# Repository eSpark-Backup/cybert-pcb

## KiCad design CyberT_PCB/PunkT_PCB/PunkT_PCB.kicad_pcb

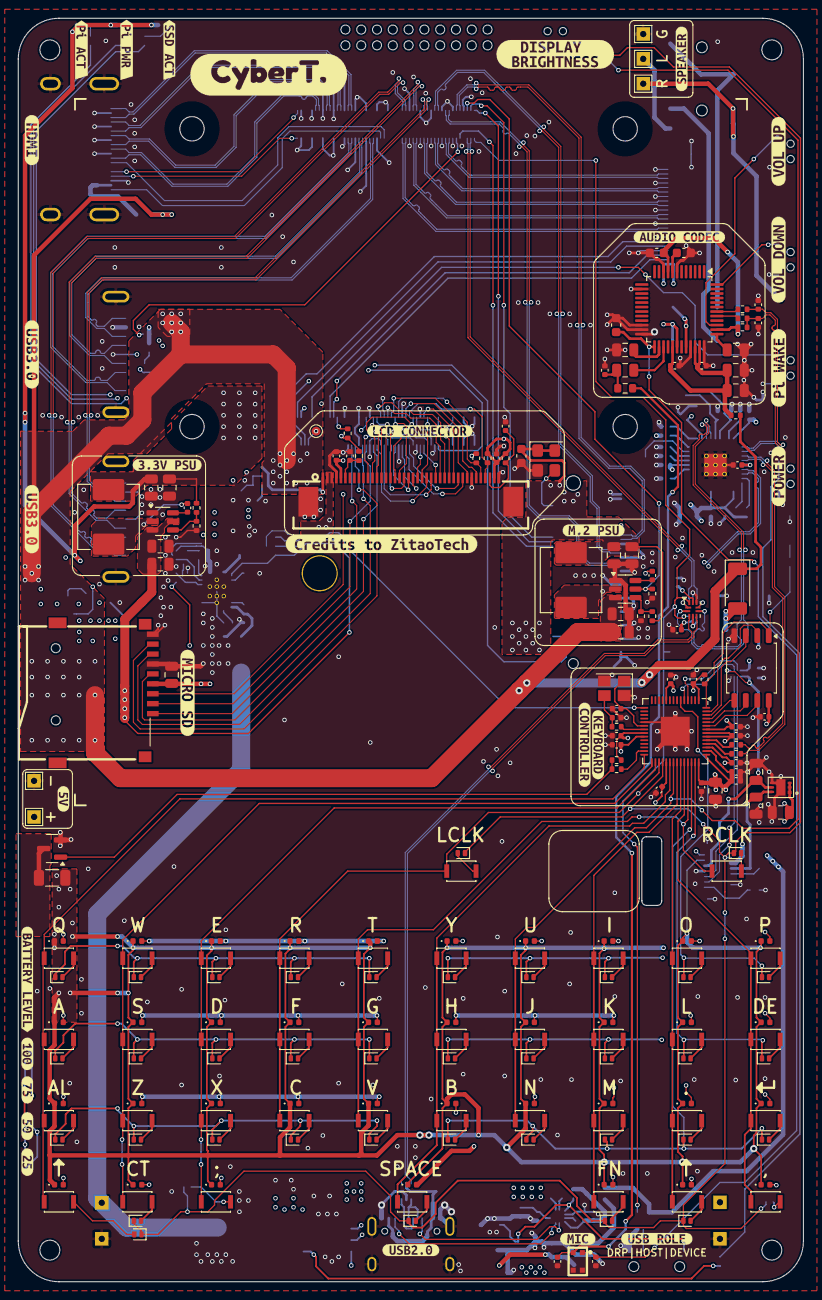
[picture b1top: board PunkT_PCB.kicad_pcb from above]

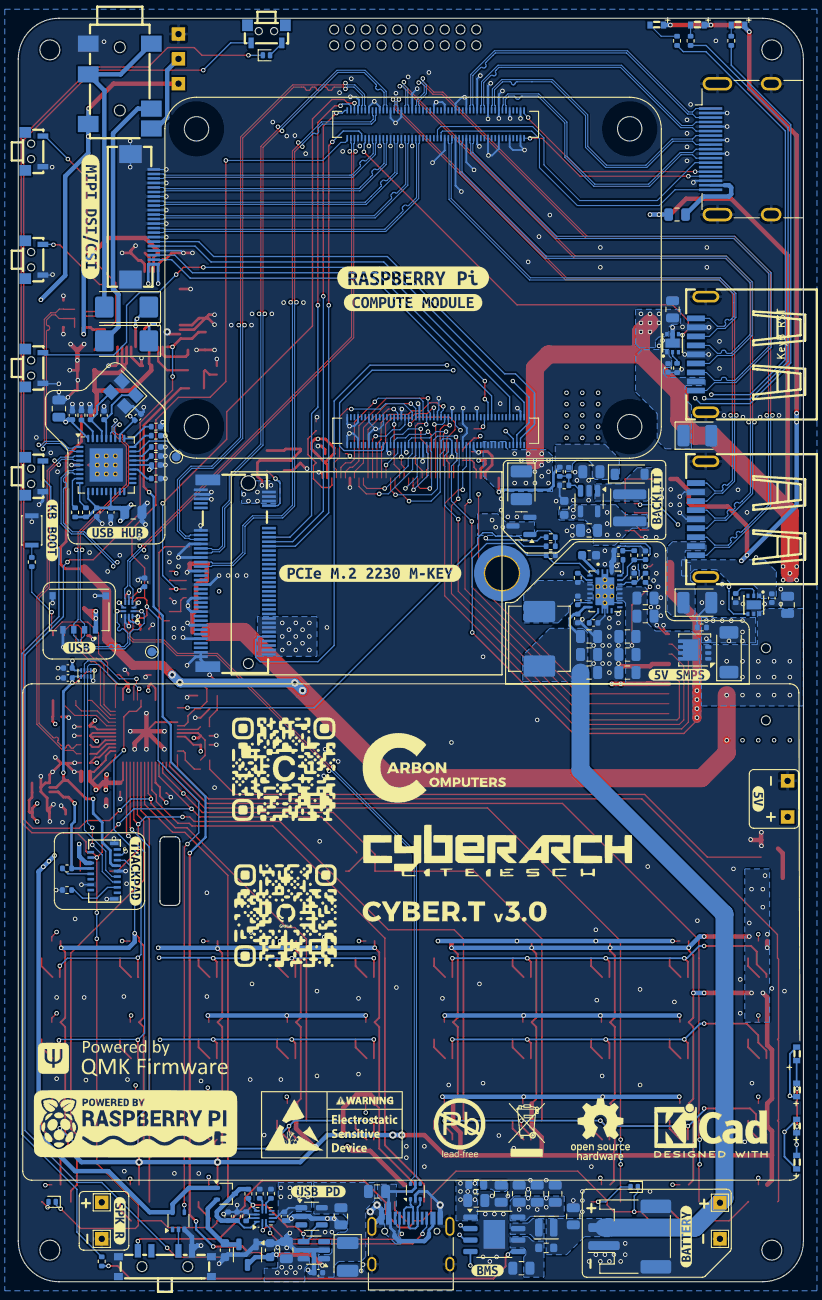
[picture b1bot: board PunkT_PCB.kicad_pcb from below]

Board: 4 copper layers, 87.0 x 140.0 mm, 405 parts (166 on the bottom side), 271 nets.

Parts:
C1, C4: 15pF; C_0402_1005Metric
C2, C10, C11, C13, C14, C15, C19, C21, C26, C30, C31, C36, C39, C43, C44, C49, C59, C60, C66, C79, C98, C101, C309, C312: 10uF; C_0805_2012Metric
C3, C5, C6, C7, C8, C9, C23, C25, C33, C40, C42, C47, C51, C56, C57, C61, C69, C70, C72, C73, C74, C75, C76, C77, C78, C81, C82, C86, C88, C96, C99, C100, C102: 0.1uF; C_0402_1005Metric
C12, C48, C58, C97: 100uF; CP_EIA-3528-21_Kemet-B
C16, C17: 470uF; CP_EIA-6032-28_Kemet-C
C18, C20: 100pF; C_0402_1005Metric
C22, C32: 22pF; C_0402_1005Metric
C24, C41, C71: 100nF; C_0402_1005Metric
C27, C28, C29, C80, C105: 4.7uF; C_0603_1608Metric
C34, C35: 33pF; C_0402_1005Metric
C37, C38, C45, C46, C50, C52, C53, C62, C63, C65, C83, C84, C85, C91, C93, C103, C104: 22uF; C_0805_2012Metric
C64: 0.1uF; C_0603_1608Metric
C67, C68, C95: 1uF; C_0402_1005Metric
C87, C310: 2.2uF; C_0603_1608Metric
C90: 8.2nF; C_0402_1005Metric
C92: 1nF; C_0402_1005Metric
C94: 47pF; C_0402_1005Metric
C311: 220pF; C_0402_1005Metric
D1, D6, D7, D8, D9, D11, D12, D13, D14, D15, D16, D17, D18, D20, D21, D22, D25, D26, D27, D30, D31, D32, D33, D35, D36, D37, D40, D41, D42, D43, D45, D46, D47, D48, D50, D51, D52, D53, D77, D81: D; D_SOD-882D
D2: PMEG2010ER,115; D_SOD-123
D3: Pi ACT; LED-SMD_XL-1606
D4: RPI PWR; LED-SMD_XL-1606
D10: PMEG4030EP,115; D_SOD-128
D19: LD1; LED-SMD_XL-1606
D23: LD2; LED-SMD_XL-1606
D24: LD3; LED-SMD_XL-1606
D28: LD4; LED-SMD_XL-1606
D29, D34, D38, D39, D44, D49, D54, D55, D56, D57, D58, D59, D60, D61, D62, D63, D64, D65, D66, D67, D68, D69, D70, D71, D72, D73, D74, D76, D78, D79, D80, D82, D83, D84, D85, D86, D87: LED; LED_0402_1005Metric
D75: BAT54CW; SOT-323_SC-70
D88: PCIe ACT; LED-SMD_XL-1606
D89: PMEG4050EP; D_SOD-128
F1: 200mA; Fuse_0805_2012Metric
H5: KEY; MountingHole_2.7mm_M2.5_DIN965_Pad_TopBottom
J1: SPK_L; TestPoint_THTPad_1.5x1.5mm_Drill0.7mm
J2: HDMI_A_1.4; HDMI_A_Molex_208658-1001_Horizontal
J3: CSI 1; FFC-SMD_22P-P0.50_X05A20L22T
J4, J21: SPK_R; TestPoint_THTPad_1.5x1.5mm_Drill0.7mm
J5: Micro_SD_Card; TF-SMD_TF-01A
J6, J22: SPK_GND; TestPoint_THTPad_1.5x1.5mm_Drill0.7mm
J7: USB; MOLEX_0781710004
J8: BATTERY; JST_PH_S2B-PH-SM4-TB_1x02-1MP_P2.00mm_Horizontal
J9: AFC07-S40ECA-00
J10: BAT+; TestPoint_THTPad_1.5x1.5mm_Drill0.7mm
J11: HEADPHONE; AUDIO-SMD_PJ-3420-A-SMT_C319102
J12: BAT-; TestPoint_THTPad_1.5x1.5mm_Drill0.7mm
J13: TYPE C; USB_C_Receptacle_HRO_TYPE-C-31-M-12
J14: FH35C-17S-0.3SHW(50); FPC-SMD_17P-P0.60_HRS_FH35C-17S-0.3SHW
J15, J16: CM5; REF
J17: Bus_M.2_Socket_M; PCI-APCI0079-P002A
J18, J19: U-A-39DS-Y-1
J20: display; REF
J23: +5V; TestPoint_THTPad_1.5x1.5mm_Drill0.7mm
J24: GND; TestPoint_THTPad_1.5x1.5mm_Drill0.7mm
L1: BLM18BD252SN1; R_0603_1608Metric
L2: 1uH; L_Sunlord_SWPA252012S
L3, L5: MWSA0618S-2R2MT; L_Sunlord_MWSA0618S
L4: MWSA0624S-1R0MT; L_Sunlord_MWSA0624S
L9: PSBHAA201210H-681T040; C_0805_2012Metric
L30: SWPA4012S100MT; L_Sunlord_SWPA4010S
Q1: DMP3013SFV; Diodes_PowerDI3333-8
Q2, Q3: AO3400A; SOT-23
R1: 2R; R_0603_1608Metric
R2, R8, R21, R24, R29, R33, R35, R44, R46, R50, R51: 10k; R_0402_1005Metric
R3, R4, R18, R19, R52: 1k; R_0402_1005Metric
R5: 120k; R_0402_1005Metric
R6, R41: 33.2k; R_0402_1005Metric
R7, R14, R42: 0R; R_0402_1005Metric
R9, R22, R26, R27, R53: 100k; R_0402_1005Metric
R10, R11, R13, R15: 36k; R_0402_1005Metric
R12: 12k; R_0402_1005Metric
R16, R17, R43, R45: 22R; R_0402_1005Metric
R20: 10.5k; R_0402_1005Metric
R23: 1.5k; R_0402_1005Metric
R25, R28, R30: 10K; R_0402_1005Metric
R31, R38: 15k; R_0402_1005Metric
R32, R49: 220R; R_0402_1005Metric
R34: 10R; R_1206_3216Metric
R36: 0.5R; R_0603_1608Metric
R39, R40: 5.1k; R_0402_1005Metric
R56: 267k; R_0402_1005Metric
R57: 113k; R_0402_1005Metric
R58: 23.7k; R_0402_1005Metric
R59: 220k; R_0402_1005Metric
R60: 69.8k; R_0402_1005Metric
SW1: PI WAKEUP; KEY-SMD_TX-1010-X-X
SW2: RESET; SW_SPST_CK_KXT3
SW3: VOL DWN; KEY-SMD_TX-1010-X-X
SW4, SW5, SW6, SW7, SW9, SW10, SW11, SW12, SW13, SW14, SW15, SW16, SW18, SW19, SW20, SW22, SW23, SW24, SW25, SW26, SW28, SW29, SW30, SW31, SW33, SW34, SW35, SW38, SW39, SW40, SW41, SW43, SW44, SW45, SW46, SW48, SW49, SW50, SW51: key; SW_SPST_CK_KXT3
SW8: VOL UP; KEY-SMD_TX-1010-X-X
SW17: POWER; KEY-SMD_TX-1010-X-X
SW21: DIPLAY BACKLIT; KEY-SMD_TX-1010-X-X
SW27: SSSS812201
TP5, TP11: nEXTRST; TestPoint_Pad_D1.0mm
TP12: nPiBOOT; TestPoint_Pad_D1.0mm
U1, U15: TPS565208DDCR; SOT-23-6
U2: TXS0102DQE; X2SON-8_1.4x1mm_P0.35mm
U3: USB2514B_Bi; QFN-36-1EP_6x6mm_P0.5mm_EP3.7x3.7mm_ThermalVias
U5, U16: TS3USB30ERSWR; UQFN-10_1.4x1.8mm_P0.4mm
U6: RPi-CM5; Raspberry-Pi-5-Compute-Module
U7: SN74LVC1G07DCKR; SOT-353_SC-70-5
U8: S15OT421-005; MIC-SMD_4P-L2.8-W1.9_S15OT421-005
U9: CM108; LQFP-48_7x7mm_P0.5mm
U10: USBLC6-2P6; SOT-666
U12, U13: AP2553FDC-7; WDFN-6_L2.0-W2.0-P0.65-BL-EP-1
U17: RP2040; QFN-56-1EP_7x7mm_P0.4mm_EP3.2x3.2mm
U18: IP5306; HTSOP-8-1EP_3.9x4.9mm_P1.27mm_EP2.4x3.2mm
U19: W25Q128JVS; SOIC-8_5.3x5.3mm_P1.27mm
U21: VRD1828MLX; LLP-6_L2.0-W1.8-P0.50-BL-EP
U22: TPS61088RHLR; IC_TPS61088RHLR
U23: XC6206PxxxMR; SOT-23-3
U25: FUSB303BTMX; Texas_X2QFN-12_1.6x1.6mm_P0.4mm
U26: AP22814AW5; SOT-23-5
U27: AP22814BW5; SOT-23-5
U57: LMR62014XMFX; SOT-23-5
Y1: 24MHz; Crystal_SMD_Abracon_ABM8G-4Pin_3.2x2.5mm
Y2: 12MHz; Crystal_SMD_SeikoEpson_FA238-4Pin_3.2x2.5mm
Y3: OK2JI-111-32.768K; Oscillator_SMD_SiT_PQFN-4Pin_3.2x2.5mm
kibuzzard-68A0B5B4: G***; kibuzzard-68A0B5B4
kibuzzard-68A0B5DF: G***; kibuzzard-68A0B5DF
kibuzzard-68A0B7F3: G***; kibuzzard-68A0B7F3
kibuzzard-68A0B20E: G***; kibuzzard-68A0B20E
kibuzzard-68A0B54C, kibuzzard-68A0B54C#2: G***; kibuzzard-68A0B54C
kibuzzard-68A0B61C: G***; kibuzzard-68A0B61C
kibuzzard-68A0B62B: G***; kibuzzard-68A0B62B
kibuzzard-68A0B64B: G***; kibuzzard-68A0B64B
kibuzzard-68A0B71E: G***; kibuzzard-68A0B71E
kibuzzard-68A0B217: G***; kibuzzard-68A0B217
kibuzzard-68A0B281: G***; kibuzzard-68A0B281
kibuzzard-68A0B510: G***; kibuzzard-68A0B510
kibuzzard-68A0B518: G***; kibuzzard-68A0B518
kibuzzard-68A0B535: G***; kibuzzard-68A0B535
kibuzzard-68A0B569: G***; kibuzzard-68A0B569
kibuzzard-68A0B633: G***; kibuzzard-68A0B633
kibuzzard-68A0B676: G***; kibuzzard-68A0B676
kibuzzard-68A0B778: G***; kibuzzard-68A0B778
kibuzzard-68A0B782: G***; kibuzzard-68A0B782
kibuzzard-68A77CD8: G***; kibuzzard-68A77CD8
kibuzzard-68A77CF1: G***; kibuzzard-68A77CF1
kibuzzard-68A77E8B: G***; kibuzzard-68A77E8B
kibuzzard-68A770D3, kibuzzard-68A770D3#2: G***; kibuzzard-68A770D3
kibuzzard-68A771D4: G***; kibuzzard-68A771D4
kibuzzard-68A772E8: G***; kibuzzard-68A772E8
kibuzzard-68A773B1: G***; kibuzzard-68A773B1
kibuzzard-68A777A6: G***; kibuzzard-68A777A6
kibuzzard-68A777CE: G***; kibuzzard-68A777CE
kibuzzard-68A777FF: G***; kibuzzard-68A777FF
kibuzzard-68A778E8: G***; kibuzzard-68A778E8
kibuzzard-68A778EF: G***; kibuzzard-68A778EF
kibuzzard-68A778FF: G***; kibuzzard-68A778FF
kibuzzard-68A788C5: G***; kibuzzard-68A788C5
kibuzzard-68A7778C: G***; kibuzzard-68A7778C
kibuzzard-68A7792B: G***; kibuzzard-68A7792B
kibuzzard-68A77223: G***; kibuzzard-68A77223
kibuzzard-68A77349: G***; kibuzzard-68A77349
kibuzzard-68A77437: G***; kibuzzard-68A77437
kibuzzard-68A77588: G***; kibuzzard-68A77588
kibuzzard-68A77715: G***; kibuzzard-68A77715
kibuzzard-68A77820: G***; kibuzzard-68A77820
kibuzzard-68A77953: G***; kibuzzard-68A77953
kibuzzard-68A79058: G***; kibuzzard-68A79058

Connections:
+1V1: C67.1, C69.1, C70.1, U17.23 (DVDD), U17.45 (VREG_VOUT), U17.50 (DVDD)
+1V8: C19.1, C24.1, J14.7, U2.1 (VCCA), U2.5 (OE), U21.5 (VOUT1)
+2V8: C15.1, J14.8, R35.1, U21.6 (VOUT2)
+3.3V: C2.1, C3.1, C5.1, C6.1, C7.1, C8.1, C9.1, C10.1, C11.1, C14.1, C40.1, C41.1, C42.1, C56.1, C57.1, C68.1, C71.1, C72.1, C73.1, C74.1, C75.1, C76.1, C77.1, C78.1, C79.1, C103.1, C104.1, D3.2 (A), D4.2 (A), D75.1, D88.2 (A), J3.22, J5.4 (VDD), J9.5, J9.39, J14.6, L5.2, R6.1, R14.1, R21.2, R22.1, R25.2, R28.2, R30.2, R39.1, R40.1, R42.1, R50.1, R51.1, U2.8 (VCCB), U3.5 (VDDA33), U3.10 (VDDA33), U3.15 (VDD33), U3.23 (VDD33), U3.29 (VDDA33), U3.36 (VDDA33), U5.9 (VCC), U7.5 (VCC), U16.9 (VCC), U17.1 (IOVDD), U17.10 (IOVDD), U17.22 (IOVDD), U17.33 (IOVDD), U17.42 (IOVDD), U17.43 (ADC_AVDD), U17.44 (VREG_IN), U17.48 (USB_VDD), U17.49 (IOVDD), U19.8 (VCC), U21.1 (EN2), U21.2 (VIN), U21.3 (EN1)
+3.3VP: C62.1, C63.1, C64.1, J17.2 (3.3V), J17.4 (3.3V), J17.12 (3.3V), J17.14 (3.3V), J17.16 (3.3V), J17.18 (3.3V), J17.70 (3.3V), J17.72 (3.3V), J17.74 (3.3V), L3.2, R41.1, Y3.1 (OE), Y3.4 (Vdd)
+5V: C12.1, C44.1, C49.1, C59.1, C60.1, C101.1, C309.1, C310.1, D10.1 (K), D29.2 (A), D34.2 (A), D38.2 (A), D39.2 (A), D44.2 (A), D49.2 (A), D54.2 (A), D55.2 (A), D56.2 (A), D57.2 (A), D58.2 (A), D59.2 (A), D60.2 (A), D61.2 (A), D62.2 (A), D63.2 (A), D64.2 (A), D65.2 (A), D66.2 (A), D67.2 (A), D68.2 (A), D69.2 (A), D70.2 (A), D71.2 (A), D72.2 (A), D73.2 (A), D74.2 (A), D76.2 (A), D78.2 (A), D79.2 (A), D80.2 (A), D82.2 (A), D83.2 (A), D84.2 (A), D85.2 (A), D86.2 (A), D87.2 (A), D89.1 (K), F1.2, J23.1, L30.1, Q1.1 (S), Q1.2 (S), Q1.3 (S), R7.1, U6.77 (+5v_(Input)), U6.79 (+5v_(Input)), U6.81 (+5v_(Input)), U6.83 (+5v_(Input)), U6.85 (+5v_(Input)), U6.87 (+5v_(Input)), U12.6 (IN), U13.6 (IN), U15.3 (VIN), U27.5 (IN), U57.4 (EN), U57.5 (VIN)
+5VA: C21.1, C23.1, C25.1, C26.1, R7.2, U9.29 (AVDD), U9.34 (AVDD), U9.35 (DVDD)
+5VL: C13.1, C50.1, C52.1, C65.1, C66.1, R33.2, U1.3 (VIN), U1.5 (EN), U18.8 (VOUT), U22.2 (EN)
+BATT: C45.1, C83.2, C84.2, C85.2, C86.2, J8.2, J10.1, L2.2, L4.1, R36.2, U22.9 (VIN)
/AUDIO IO/USB1_D+: C18.1, R23.2, R43.2, U3.2 (USBDP_DN1/PRT_DIS_P1)
/AUDIO IO/USB1_D-: C20.1, R45.2, U3.1 (USBDM_DN1/PRT_DIS_M1)
/AUDIO IO/VBIAS: C27.1, C33.1, U8.1 (VDD), U9.25 (VBIAS)
/AUDIO IO/VOL_DWN: SW3.2, U9.48 (VOLDN)
/AUDIO IO/VOL_UP: SW8.2, U9.39 (VOLUP)
/CM5/ACT_LED: R3.1, U6.21 (LED_nACT)
/CM5/B2: J9.16, U6.27 (GPIO20)
/CM5/B3: J9.17, U6.25 (GPIO21)
/CM5/B4: J9.18, U6.46 (GPIO22)
/CM5/B5: J9.19, U6.47 (GPIO23)
/CM5/B6: J9.20, U6.45 (GPIO24)
/CM5/B7: J9.21, U6.41 (GPIO25)
/CM5/CAM1_C_N: J3.8, U6.127 (MIPI0_C_N)
/CM5/CAM1_C_P: J3.9, U6.129 (MIPI0_C_P)
/CM5/CAM1_D0_N: J3.2, U6.115 (MIPI0_D0_N)
/CM5/CAM1_D0_P: J3.3, U6.117 (MIPI0_D0_P)
/CM5/CAM1_D1_N: J3.5, U6.121 (MIPI0_D1_N)
/CM5/CAM1_D1_P: J3.6, U6.123 (MIPI0_D1_P)
/CM5/CAM1_D2_N: J3.11, U6.133 (MIPI0_D2_N)
/CM5/CAM1_D2_P: J3.12, U6.135 (MIPI0_D2_P)
/CM5/CAM1_D3_N: J3.14, U6.139 (MIPI0_D3_N)
/CM5/CAM1_D3_P: J3.15, U6.141 (MIPI0_D3_P)
/CM5/CAM_GPIO0: J3.17, U6.97 (CAM_GPIO0)
/CM5/CAM_GPIO1: J3.18, U6.100 (CAM_GPIO1)
/CM5/CM5_OTG_ID: TP5.1, U5.10 (S), U6.101 (USB_OTG_ID), U7.4, U16.10 (S)
/CM5/DISP_CS: J9.11, U6.49 (GPIO18)
/CM5/DISP_DE: J9.13, U6.35 (ID_SC)
/CM5/DISP_PCLK: J9.12, U6.36 (ID_SD)
/CM5/G2: J9.22, U6.31 (GPIO12)
/CM5/G3: J9.23, U6.28 (GPIO13)
/CM5/G4: J9.24, U6.55 (GPIO14)
/CM5/G5: J9.25, U6.51 (GPIO15)
/CM5/G6: J9.26, U6.29 (GPIO16)
/CM5/G7: J9.27, U6.50 (GPIO17)
/CM5/HDMI0_CEC: J2.13 (CEC), U6.151 (HDMI0_CEC)
/CM5/HDMI0_CLK_N: J2.12 (CK-), U6.190 (HDMI0_CLK_N)
/CM5/HDMI0_CLK_P: J2.10 (CK+), U6.188 (HDMI0_CLK_P)
/CM5/HDMI0_HP: J2.19 (HPD/HEAC-), U6.153 (HDMI0_HOTPLUG)
/CM5/HDMI0_SCL: J2.15 (SCL), U6.200 (HDMI0_SCL)
/CM5/HDMI0_SDA: J2.16 (SDA), U6.199 (HDMI0_SDA)
/CM5/HDMI0_TX0_N: J2.9 (D0-), U6.184 (HDMI0_TX0_N)
/CM5/HDMI0_TX0_P: J2.7 (D0+), U6.182 (HDMI0_TX0_P)
/CM5/HDMI0_TX1_N: J2.6 (D1-), U6.178 (HDMI0_TX1_N)
/CM5/HDMI0_TX1_P: J2.4 (D1+), U6.176 (HDMI0_TX1_P)
/CM5/HDMI0_TX2_N: J2.3 (D2-), U6.172 (HDMI0_TX2_N)
/CM5/HDMI0_TX2_P: J2.1 (D2+), U6.170 (HDMI0_TX2_P)
/CM5/HSYNC: J9.15, U6.56 (GPIO3)
/CM5/PCIE_CLK_N: J17.53 (REFCLKn), U6.112 (PCIe_CLK_N)
/CM5/PCIE_CLK_P: J17.55 (REFCLKp), U6.110 (PCIe_CLK_P)
/CM5/PCIE_PWR_EN: R9.1, U6.106 (PCIE_PWR_EN), U15.5 (EN)
/CM5/PCIE_RX_N: J17.41 (PERn0/SATA-B+), U6.118 (PCIe_RX_N)
/CM5/PCIE_RX_P: J17.43 (PERp0/SATA-B-), U6.116 (PCIe_RX_P)
/CM5/PCIE_TX_N: J17.49 (PETp0/SATA-A+), U6.124 (PCIe_TX_N)
/CM5/PCIE_TX_P: J17.47 (PETn0/SATA-A-), U6.122 (PCIe_TX_P)
/CM5/PCIE_nCLKREQ: J17.52 (~CLKREQ), U6.102 (PCIe_nCLKREQ)
/CM5/PCIE_nRST: J17.50 (~PERST), U6.109 (PCIe_nRST)
/CM5/PCIE_nWAKE: J17.54 (~PEWAKE), U6.104 (PCIE_nWAKE)
/CM5/PWR_BUT: SW1.2, U6.92 (PWR_BUT)
/CM5/R2: J9.28, U6.54 (GPIO4)
/CM5/R3: J9.29, U6.34 (GPIO5)
/CM5/R4: J9.30, U6.30 (GPIO6)
/CM5/R5: J9.31, U6.37 (GPIO7)
/CM5/R6: J9.32, U6.39 (GPIO8)
/CM5/R7: J9.33, U6.40 (GPIO9)
/CM5/SCL: J9.37, R39.2, U6.38 (GPIO11)
/CM5/SCL0: J3.20, U6.80 (SCL0)
/CM5/SDA: J9.36, R40.2, U6.44 (GPIO10)
/CM5/SDA0: J3.21, U6.82 (SDA0)
/CM5/SD_CLK: J5.5 (CLK), U6.57 (SD_CLK)
/CM5/SD_CMD: J5.3 (CMD), U6.62 (SD_CMD)
/CM5/SD_D0: J5.7 (DAT0), U6.63 (SD_DAT0)
/CM5/SD_D1: J5.8 (DAT1), U6.67 (SD_DAT1)
/CM5/SD_D2: J5.1 (DAT2), U6.69 (SD_DAT2)
/CM5/SD_D3: J5.2 (DAT3/CD), U6.61 (SD_DAT3)
/CM5/TOUCH_INT: J9.35, U6.48 (GPIO27)
/CM5/USB3-0-D_N: J18.2 (D-), U6.136 (USB3-0-D_N)
/CM5/USB3-0-D_P: J18.3 (D+), U6.134 (USB3-0-D_P)
/CM5/USB3-0-RX_N: J18.5 (SSRX-), U6.128 (USB3-0-RX_N)
/CM5/USB3-0-RX_P: J18.6 (SSRX+), U6.130 (USB3-0-RX_P)
/CM5/USB3-0-TX_N: J18.8 (SSTX-), U6.140 (USB3-0-TX_N)
/CM5/USB3-0-TX_P: J18.9 (SSTX+), U6.142 (USB3-0-TX_P)
/CM5/USB3-1-D_N: J19.2 (D-), U6.165 (USB3-1-D_N)
/CM5/USB3-1-D_P: J19.3 (D+), U6.163 (USB3-1-D_P)
/CM5/USB3-1-RX_N: J19.5 (SSRX-), U6.157 (USB3-1-RX_N)
/CM5/USB3-1-RX_P: J19.6 (SSRX+), U6.159 (USB3-1-RX_P)
/CM5/USB3-1-TX_N: J19.8 (SSTX-), U6.169 (USB3-1-TX_N)
/CM5/USB3-1-TX_P: J19.9 (SSTX+), U6.171 (USB3-1-TX_P)
/CM5/USB_CM5_D+: U6.105 (USB2_P), U16.3 (D+)
/CM5/USB_CM5_D-: U6.103 (USB2_N), U16.5 (D-)
/CM5/VBUS_EN: U6.111 (VBUS_EN), U12.4 (EN), U13.4 (EN)
/CM5/VSYNC: J9.14, U6.58 (GPIO2)
/CM5/nEXTRST: TP11.1, U3.26 (RESET_N)
/CM5/nPWR_LED: R4.1, U6.95 (LED_nPWR)
/DISPLAY/DISPLAY_BACKLIT: R32.2, U17.15 (GPIO12)
/DISPLAY/DISP_RESET: C82.2, J9.6, R28.1
/DISPLAY/LED_A: C311.1, C312.1, D2.1 (K), J9.1, R5.1
/DISPLAY/LED_K: J9.2, J9.3, Q3.3 (D)
/DISPLAY/TP_RESET: C81.2, J9.38, R25.1
/KEYPAD/BL_K: D29.1 (K), D34.1 (K), D38.1 (K), D39.1 (K), D44.1 (K), D49.1 (K), D54.1 (K), D55.1 (K), D56.1 (K), D57.1 (K), D58.1 (K), D59.1 (K), D60.1 (K), D61.1 (K), D62.1 (K), D63.1 (K), D64.1 (K), D65.1 (K), D66.1 (K), D67.1 (K), D68.1 (K), D69.1 (K), D70.1 (K), D71.1 (K), D72.1 (K), D73.1 (K), D74.1 (K), D76.1 (K), D78.1 (K), D79.1 (K), D80.1 (K), D82.1 (K), D83.1 (K), D84.1 (K), D85.1 (K), D86.1 (K), D87.1 (K), J14.5, R34.2
/KEYPAD/COL0: SW4.1, SW5.1, SW6.1, SW7.1, U17.28 (GPIO17)
/KEYPAD/COL1: SW9.1, SW10.1, SW11.1, SW12.1, U17.29 (GPIO18)
/KEYPAD/COL2: SW13.1, SW14.1, SW15.1, SW16.1, U17.30 (GPIO19)
/KEYPAD/COL3: J14.3, SW18.1, SW19.1, SW20.1, SW22.1, U17.31 (GPIO20)
/KEYPAD/COL4: SW23.1, SW24.1, SW25.1, SW26.1, U17.39 (GPIO27_ADC1)
/KEYPAD/COL5: SW28.1, SW29.1, SW30.1, SW31.1, U17.34 (GPIO22)
/KEYPAD/COL6: SW21.1, SW33.1, SW34.1, SW35.1, U17.35 (GPIO23)
/KEYPAD/COL7: SW38.1, SW39.1, SW40.1, SW41.1, U17.36 (GPIO24)
/KEYPAD/COL8: SW43.1, SW44.1, SW45.1, SW46.1, U17.37 (GPIO25)
/KEYPAD/COL9: SW48.1, SW49.1, SW50.1, SW51.1, U17.38 (GPIO26_ADC0)
/KEYPAD/KP_BL_K: R49.1, U17.27 (GPIO16)
/KEYPAD/QSPI_SCLK: U17.52 (QSPI_SCLK), U19.6 (CLK)
/KEYPAD/QSPI_SD0: U17.53 (QSPI_SD0), U19.5 (DI(IO0))
/KEYPAD/QSPI_SD1: U17.55 (QSPI_SD1), U19.2 (DO(IO1))
/KEYPAD/QSPI_SD2: U17.54 (QSPI_SD2), U19.3 (IO2)
/KEYPAD/QSPI_SD3: U17.51 (QSPI_SD3), U19.7 (IO3)
/KEYPAD/QSPI_SS: R19.2, R22.2, U17.56 (QSPI_SS), U19.1 (~CS)
/KEYPAD/ROW0: D6.1 (K), D11.1 (K), D15.1 (K), D20.1 (K), D25.1 (K), D30.1 (K), D35.1 (K), D40.1 (K), D45.1 (K), D50.1 (K), U17.6 (GPIO4)
/KEYPAD/ROW1: D7.1 (K), D12.1 (K), D16.1 (K), D21.1 (K), D26.1 (K), D31.1 (K), D36.1 (K), D41.1 (K), D46.1 (K), D51.1 (K), U17.41 (GPIO29_ADC3)
/KEYPAD/ROW2: D8.1 (K), D13.1 (K), D17.1 (K), D22.1 (K), D27.1 (K), D32.1 (K), D37.1 (K), D42.1 (K), D47.1 (K), D52.1 (K), U17.40 (GPIO28_ADC2)
/KEYPAD/ROW3: D1.1 (K), D9.1 (K), D14.1 (K), D18.1 (K), D33.1 (K), D43.1 (K), D48.1 (K), D53.1 (K), D77.1 (K), D81.1 (K), J14.4, U17.32 (GPIO21)
/KEYPAD/RP2040_I2C_SCL: U2.6 (B2), U17.5 (GPIO3)
/KEYPAD/RP2040_I2C_SDA: U2.7 (B1), U17.4 (GPIO2)
/KEYPAD/TP_I2C_SCL: J14.13, U2.3 (A2)
/KEYPAD/TP_I2C_SDA: J14.11, U2.2 (A1)
/KEYPAD/USB2_D+: R16.2, U3.4 (USBDP_DN2/PRT_DIS_P2)
/KEYPAD/USB2_D-: R17.2, U3.3 (USBDM_DN2/PRT_DIS_M2)
/KEYPAD/USB_BOOT: R19.1, SW2.1
/USB & PCIe/VBUS1: C51.1, C58.1, J18.1 (VBUS), U12.1 (OUT)
/USB & PCIe/VBUS2: C47.1, C48.1, J19.1 (VBUS), U13.1 (OUT)
/USB CONNECTOR/CC1: J13.A5 (CC1), U25.1 (CC1)
/USB CONNECTOR/CC2: J13.B5 (CC2), U25.2 (CC2)
/USB CONNECTOR/TYPE_C_D+: U5.3 (D+), U10.4 (I/O2)
/USB CONNECTOR/TYPE_C_D-: U5.5 (D-), U10.6 (I/O1)
/USB CONNECTOR/USB_ID: R8.1, SW27.1, U25.9 (ID), U26.4 (EN), U27.4 (~EN)
/USB CONNECTOR/VUSB: C97.1, C98.1, C99.1, C105.1, L9.1, U23.3 (VI), U26.5 (IN), U27.1 (OUT)
/USB HUB/USB3_D+: U3.7 (USBDP_DN3/PRT_DIS_P3), U5.1 (D1+), U16.2 (D2+)
/USB HUB/USB3_D-: U3.6 (USBDM_DN3/PRT_DIS_M3), U5.7 (D1-), U16.6 (D2-)
/USB HUB/USB_HUB_UP_D+: J7.3, U3.31 (USBDP_UP), U5.2 (D2+), U16.1 (D1+)
/USB HUB/USB_HUB_UP_D-: J7.2, U3.30 (USBDM_UP), U5.6 (D2-), U16.7 (D1-)
/USB HUB/XI: C4.1, U3.33 (XTALIN/CLKIN), Y1.3
/USB HUB/XO: C1.1, U3.32 (XTALOUT), Y1.1
COdeC3V3: C28.1, R23.1, U9.9 (DREG33), U9.38 (MSEL)
GND: C1.2, C2.2, C3.2, C4.2, C5.2, C6.2, C7.2, C8.2, C9.2, C10.2, C11.2, C12.2, C13.2, C14.2, C15.2, C18.2, C19.2, C20.2, C21.2, C22.2, C23.2, C24.2, C25.2, C26.2, C27.2, C28.2, C29.2, C30.2, C31.2, C32.2, C33.2, C34.2, C35.2, C37.1, C38.1, C39.2, C40.2, C41.2, C42.2, C43.2, C44.2, C45.2, C46.2, C47.2, C48.2, C49.2, C50.2, C51.2, C52.2, C53.1, C56.2, C57.2, C58.2, C59.2, C60.2, C62.2, C63.2, C64.2, C65.2, C66.2, C67.2, C68.2, C69.2, C70.2, C71.2, C72.2, C73.2, C74.2, C75.2, C76.2, C77.2, C78.2, C79.2, C80.2, C81.1, C82.1, C83.1, C84.1, C85.1, C86.1, C87.1, C90.1, C91.1, C92.1, C93.1, C94.1, C95.2, C96.2, C97.2, C98.2, C99.2, C100.2, C101.2, C103.2, C104.2, C105.2, C309.2, C310.2, C312.2, J2.2 (D2S), J2.5 (D1S), J2.8 (D0S), J2.11 (CKS), J2.17 (GND), J2.SH, J3.1, J3.4, J3.7, J3.10, J3.13, J3.16, J3.19, J3.MP (MountPin), J5.6 (VSS), J5.9 (SHIELD), J6.1, J7.4, J7.MP (MountPin), J8.1, J8.MP (MountPin), J9.4, J9.34, J9.40, J9.MP (MountPin), J11.S, J12.1, J13.A1 (GND), J13.A12 (GND), J13.B1 (GND), J13.B12 (GND), J13.S1 (SHIELD), J14.9, J14.14, J14.MP (MountPin), J17.1 (GND), J17.3 (GND), J17.9 (GND), J17.15 (GND), J17.21 (GND), J17.27 (GND), J17.33 (GND), J17.39 (GND), J17.45 (GND), J17.51 (GND), J17.57 (GND), J17.71 (GND), J17.73 (GND), J17.75 (GND), J18.4 (GND), J18.7 (DRAIN), J18.10 (SHIELD), J19.4 (GND), J19.7 (DRAIN), J19.10 (SHIELD), J22.1, J24.1, Q2.2 (S), Q3.2 (S), R2.1, R9.2, R10.2, R11.2, R12.2, R13.2, R15.2, R20.2, R26.1, R27.1, R29.2, R31.1, R33.1, R38.1, R44.2, R46.2, R53.1, R57.1, R60.1, SW1.1, SW2.2, SW3.1, SW8.1, SW17.1, SW27.4, U1.1 (GND), U2.4 (GND), U3.37 (VSS), U5.4 (GND), U5.8 (~OE), U6.1 (GND), U6.2 (GND), U6.7 (GND), U6.8 (GND), U6.13 (GND), U6.14 (GND), U6.22 (GND), U6.23 (GND), U6.32 (GND), U6.33 (GND), U6.42 (GND), U6.43 (GND), U6.52 (GND), U6.53 (GND), U6.59 (GND), U6.60 (GND), U6.65 (GND), U6.66 (GND), U6.71 (GND), U6.74 (GND), U6.98 (GND), U6.107 (GND), U6.108 (GND), U6.113 (GND), U6.114 (GND), U6.119 (GND), U6.120 (GND), U6.125 (GND), U6.126 (GND), U6.131 (GND), U6.132 (GND), U6.137 (GND), U6.138 (GND), U6.144 (GND), U6.150 (GND), U6.155 (GND), U6.156 (GND), U6.161 (GND), U6.162 (GND), U6.167 (GND), U6.168 (GND), U6.173 (GND), U6.174 (GND), U6.179 (GND), U6.180 (GND), U6.185 (GND), U6.186 (GND), U6.191 (GND), U6.192 (GND), U6.197 (GND), U6.198 (GND), U7.3 (GND), U8.2 (GND), U8.3 (GND), U9.7 (PWRSEL), U9.10 (MODE), U9.14 (DVSS), U9.22 (ADSEL), U9.23 (TEST), U9.24 (AVSS), U9.33 (AVSS), U9.36 (DVSS), U10.2 (GND), U12.5 (GND), U12.7 (GND), U13.5 (GND), U13.7 (GND), U15.1 (GND), U16.4 (GND), U16.8 (~OE), U17.19 (TESTEN), U17.57 (GND), U18.9 (GND), U19.4 (GND), U21.4 (VSS), U21.7 (VSS), U22.13 (MODE), U22.20 (AGND), U22.21 (PGND), U23.1 (GND), U25.10 (GND), U26.2 (GND), U27.2 (GND), U57.2 (GND), Y1.2, Y1.4, Y2.2, Y2.4, Y3.2 (GND)
unnamed: C16.2, J11.T
unnamed: C17.2, J11.R
unnamed: C32.1, R18.2, Y2.3
unnamed: C35.1, C36.1, L1.2
unnamed: C43.1, R1.2
unnamed: C88.2, L4.2, R56.2, U22.4 (SW), U22.5 (SW), U22.6 (SW), U22.7 (SW)
unnamed: C92.2, R58.1
unnamed: D1.2 (A), SW21.2
unnamed: D2.2 (A), L30.2, U57.1 (SW)
unnamed: D3.1 (K), R3.2
unnamed: D4.1 (K), R4.2
unnamed: D6.2 (A), SW4.2
unnamed: D7.2 (A), SW5.2
unnamed: D8.2 (A), SW6.2
unnamed: D9.2 (A), SW7.2
unnamed: D10.2 (A), J7.1
unnamed: D11.2 (A), SW9.2
unnamed: D12.2 (A), SW10.2
unnamed: D13.2 (A), SW11.2
unnamed: D14.2 (A), SW12.2
unnamed: D15.2 (A), SW13.2
unnamed: D16.2 (A), SW14.2
unnamed: D17.2 (A), SW15.2
unnamed: D18.2 (A), SW16.2
unnamed: D19.2 (A), D23.1 (K), U18.2 (LED1)
unnamed: D19.1 (K), D23.2 (A), D24.1 (K), D28.2 (A), U18.4 (LED3)
unnamed: D20.2 (A), SW18.2
unnamed: D21.2 (A), SW19.2
unnamed: D22.2 (A), SW20.2
unnamed: D24.2 (A), D28.1 (K), U18.3 (LED2)
unnamed: D25.2 (A), SW23.2
unnamed: D26.2 (A), SW24.2
unnamed: D27.2 (A), SW25.2
unnamed: D30.2 (A), SW28.2
unnamed: D31.2 (A), SW29.2
unnamed: D32.2 (A), SW30.2
unnamed: D33.2 (A), SW31.2
unnamed: D35.2 (A), SW33.2
unnamed: D36.2 (A), SW34.2
unnamed: D37.2 (A), SW35.2
unnamed: D40.2 (A), SW38.2
unnamed: D41.2 (A), SW39.2
unnamed: D42.2 (A), SW40.2
unnamed: D43.2 (A), SW41.2
unnamed: D45.2 (A), SW43.2
unnamed: D46.2 (A), SW44.2
unnamed: D47.2 (A), SW45.2
unnamed: D48.2 (A), SW46.2
unnamed: D50.2 (A), SW48.2
unnamed: D51.2 (A), SW49.2
unnamed: D52.2 (A), SW50.2
unnamed: D53.2 (A), SW51.2
unnamed: D77.2 (A), SW22.2
unnamed: D81.2 (A), SW26.2
unnamed: D88.1 (K), R52.2
unnamed: J1.1, J11.TN
unnamed: F1.1, J2.18 (+5V)
unnamed: J13.A6 (D+), J13.B6 (D+), U10.3 (I/O2)
unnamed: J13.A7 (D-), J13.B7 (D-), U10.1 (I/O1)
unnamed: J14.10, R35.2
unnamed: J14.15, R46.1
unnamed: J17.10 (DAS/~DSS/~LED1), R52.1
unnamed: J17.68 (SUSCLK), Y3.3 (OUT)
unnamed: J4.1, J11.RN, J21.1
unnamed: C37.2, C38.2, C53.2, C91.2, C93.2, Q1.5 (D), R59.2, U22.14 (VOUT), U22.15 (VOUT), U22.16 (VOUT)
unnamed: Q2.3 (D), R34.1
unnamed: Q2.1 (G), R21.1, R49.2
unnamed: Q3.1 (G), R30.1, R32.1
unnamed: R24.1, SW17.2
unnamed: SW27.3, U7.2
unnamed: C102.2, L5.1, U1.2 (SW)
unnamed: C102.1, U1.6 (VBST)
unnamed: R6.2, R29.1, U1.4 (VFB)
unnamed: R15.1, U3.25 (HS_IND/CFG_SEL1)
unnamed: R12.1, U3.35 (RBIAS)
unnamed: R10.1, U3.24 (SCL/SMBCLK/CFG_SEL0)
unnamed: R11.1, U3.22 (SDA/SMBDATA/NON_REM1)
unnamed: R13.1, U3.28 (SUSP_IND/LOCAL_PWR/NON_REM0)
unnamed: R50.2, U3.8 (USBDM_DN4/PRT_DIS_M4)
unnamed: R51.2, U3.9 (USBDP_DN4/PRT_DIS_P4)
unnamed: R14.2, U3.27 (VBUS_DET)
unnamed: R42.2, U6.78 (GPIO_VREF(1.8v/3.3v_Input))
unnamed: TP12.1, U6.93 (nRPIBOOT)
unnamed: C34.1, L1.1, U8.4 (OUT)
unnamed: C30.1, U9.37 (AREG36)
unnamed: C29.1, U9.8 (DREG18)
unnamed: C16.1, U9.30 (LOL)
unnamed: C17.1, U9.32 (LOR)
unnamed: C36.2, U9.27 (MICIN)
unnamed: R45.1, U9.42 (USBDM)
unnamed: R43.1, U9.41 (USBDP)
unnamed: C31.1, U9.26 (VREF)
unnamed: J13.A4 (VBUS), J13.A9 (VBUS), J13.B4 (VBUS), J13.B9 (VBUS), L9.2, U10.5 (VBUS)
unnamed: R38.2, U12.2 (ILIM)
unnamed: R31.2, U13.2 (ILIM)
unnamed: C61.2, L3.1, U15.2 (SW)
unnamed: C61.1, U15.6 (VBST)
unnamed: R41.2, R44.1, U15.4 (VFB)
unnamed: R17.1, U17.46 (USB_DM)
unnamed: R16.1, U17.47 (USB_DP)
unnamed: C22.1, U17.20 (XIN), Y2.1
unnamed: R18.1, U17.21 (XOUT)
unnamed: C46.1, R36.1, U18.6 (BAT)
unnamed: R24.2, U18.5 (KEY)
unnamed: L2.1, U18.7 (SW)
unnamed: C88.1, U22.8 (BOOT)
unnamed: C94.2, R58.2, U22.18 (COMP)
unnamed: R59.1, R60.2, U22.17 (FB)
unnamed: R56.1, U22.3 (FSW)
unnamed: R57.2, U22.19 (ILIM)
unnamed: C90.2, U22.10 (SS)
unnamed: C87.2, U22.1 (VCC)
unnamed: C80.1, D75.2, U23.2 (VO)
unnamed: R26.2, U25.11 (EN_N)
unnamed: R53.2, U25.8 (SCL/OUT2)
unnamed: R27.2, U25.7 (SDA/OUT1)
unnamed: C95.1, C96.1, D75.3, R8.2, U25.12 (VDD)
unnamed: C311.2, R5.2, R20.1, U57.3 (FB)
VBUS: C39.1, C100.1, D89.2 (A), Q1.4 (G), R1.1, R2.2, U18.1 (VIN), U25.4 (VBUS_DET), U26.1 (OUT)

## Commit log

2025-10-14 #1 Sch Completed
